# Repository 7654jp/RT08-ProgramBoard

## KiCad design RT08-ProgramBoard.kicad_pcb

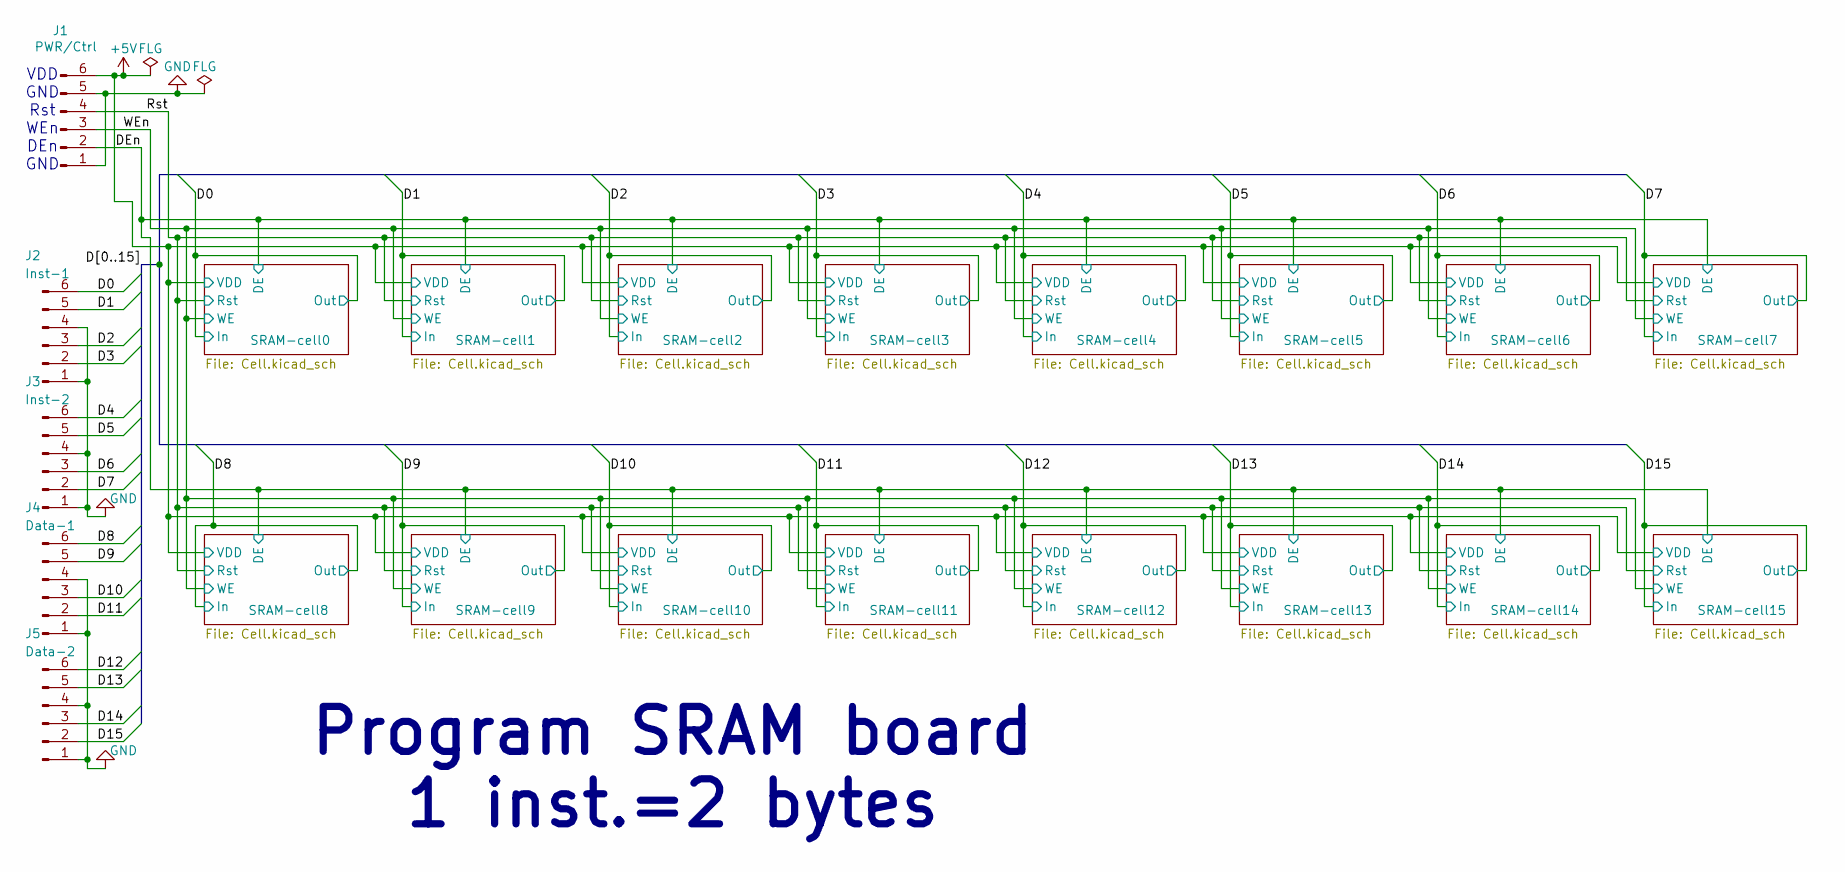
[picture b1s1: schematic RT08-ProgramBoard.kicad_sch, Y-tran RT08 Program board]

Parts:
J1: PWR/Ctrl; PinHeader_1x06_P2.54mm_Vertical
J2: Inst-1; PinHeader_1x06_P2.54mm_Vertical
J3: Inst-2; PinHeader_1x06_P2.54mm_Vertical
J4: Data-1; PinHeader_1x06_P2.54mm_Vertical
J5: Data-2; PinHeader_1x06_P2.54mm_Vertical

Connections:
+5V: J1.6; also elsewhere on the board
/D0: J2.6; also elsewhere on the board
/D1: J2.5; also elsewhere on the board
/D2: J2.3; also elsewhere on the board
/D3: J2.2; also elsewhere on the board
/D4: J3.6; also elsewhere on the board
/D5: J3.5; also elsewhere on the board
/D6: J3.3; also elsewhere on the board
/D7: J3.2; also elsewhere on the board
/D8: J4.6; also elsewhere on the board
/D9: J4.5; also elsewhere on the board
/D10: J4.3; also elsewhere on the board
/D11: J4.2; also elsewhere on the board
/D12: J5.6; also elsewhere on the board
/D13: J5.5; also elsewhere on the board
/D14: J5.3; also elsewhere on the board
/D15: J5.2; also elsewhere on the board
/DEn: J1.2; also elsewhere on the board
/Rst: J1.4; also elsewhere on the board
/WEn: J1.3; also elsewhere on the board
GND: J1.1, J1.5, J2.1, J2.4, J3.1, J3.4, J4.1, J4.4, J5.1, J5.4; also elsewhere on the board

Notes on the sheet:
VDD GND Rst WEn DEn GND
Program SRAM board 1 inst.=2 bytes

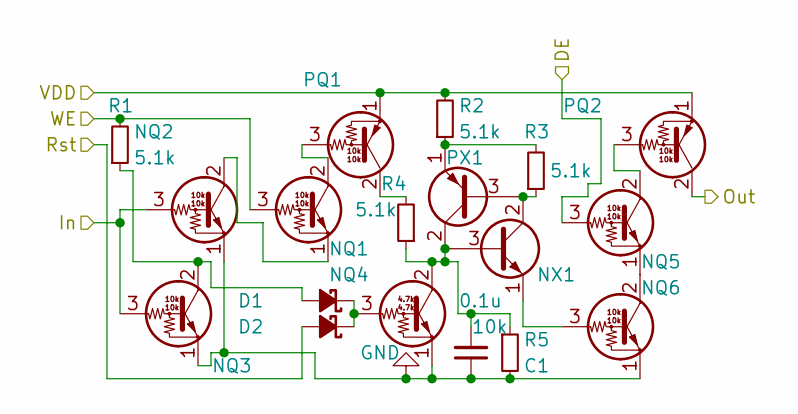
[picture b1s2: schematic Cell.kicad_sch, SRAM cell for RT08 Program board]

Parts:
C1: 0.1u; C_Disc_D3.0mm_W2.0mm_P2.50mm
D1, D2: 30V0.2A; D_DO-35_SOD27_P7.62mm_Horizontal
NQ1, NQ2, NQ3, NQ5, NQ6: DTC114E-THT; TO-92_Inline_Wide
NQ4: DTC143E-THT; TO-92_Inline_Wide
NX1: 2SC1815; TO-92_Inline_Wide
PQ1, PQ2: DTA114E-THT; TO-92_Inline_Wide
PX1: 2SA1015; TO-92_Inline_Wide
R1, R2, R3, R4: 5.1k; R_Axial_DIN0207_L6.3mm_D2.5mm_P7.62mm_Horizontal
R5: 10k; R_Axial_DIN0207_L6.3mm_D2.5mm_P7.62mm_Horizontal

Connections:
+5V: PQ1.1 (E), PQ2.1 (E), R2.2; also elsewhere on the board
/D0: NQ2.3 (B), NQ3.3 (B), PQ2.2 (C); also elsewhere on the board
/DEn: NQ5.3 (B); also elsewhere on the board
/Rst: D2.2 (A); also elsewhere on the board
/WEn: NQ1.3 (B), R1.2; also elsewhere on the board
GND: C1.1, NQ2.1 (E), NQ3.1 (E), NQ4.1 (E), NQ6.1 (E), R5.2; also elsewhere on the board
unnamed: D1.2 (A), NQ3.2 (C), R1.1
unnamed: D1.1 (K), D2.1 (K), NQ4.3 (B)
unnamed: NQ1.2 (C), PQ1.3 (B)
unnamed: NQ1.1 (E), NQ2.2 (C)
unnamed: C1.2, NQ4.2 (C), NX1.3 (B), PX1.2 (C), R4.1, R5.1
unnamed: NQ5.2 (C), PQ2.3 (B)
unnamed: NQ5.1 (E), NQ6.2 (C)
unnamed: NQ6.3 (B), NX1.1 (E)
unnamed: NX1.2 (C), PX1.3 (B), R3.1
unnamed: PQ1.2 (C), R4.2
unnamed: PX1.1 (E), R2.1, R3.2

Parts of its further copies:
C2, C3, C4, C5, C6, C7, C8, C9, C10, C11, C12, C13, C14, C15, C16: 0.1u; C_Disc_D3.0mm_W2.0mm_P2.50mm
D3, D4, D5, D6, D7, D8, D9, D10, D11, D12, D13, D14, D15, D16, D17, D18, D19, D20, D21, D22, D23, D24, D25, D26, D27, D28, D29, D30, D31, D32: 30V0.2A; D_DO-35_SOD27_P7.62mm_Horizontal
NQ7, NQ8, NQ9, NQ11, NQ12, NQ13, NQ14, NQ15, NQ17, NQ18, NQ19, NQ20, NQ21, NQ23, NQ24, NQ25, NQ26, NQ27, NQ29, NQ30, NQ31, NQ32, NQ33, NQ35, NQ36, NQ37, NQ38, NQ39, NQ41, NQ42, NQ43, NQ44, NQ45, NQ47, NQ48, NQ49, NQ50, NQ51, NQ53, NQ54, NQ55, NQ56, NQ57, NQ59, NQ60, NQ61, NQ62, NQ63, NQ65, NQ66, NQ67, NQ68, NQ69, NQ71, NQ72, NQ73, NQ74, NQ75, NQ77, NQ78, NQ79, NQ80, NQ81, NQ83, NQ84, NQ85, NQ86, NQ87, NQ89, NQ90, NQ91, NQ92, NQ93, NQ95, NQ96: DTC114E-THT; TO-92_Inline_Wide
NQ10, NQ16, NQ22, NQ28, NQ34, NQ40, NQ46, NQ52, NQ58, NQ64, NQ70, NQ76, NQ82, NQ88, NQ94: DTC143E-THT; TO-92_Inline_Wide
NX2, NX3, NX4, NX5, NX6, NX7, NX8, NX9, NX10, NX11, NX12, NX13, NX14, NX15, NX16: 2SC1815; TO-92_Inline_Wide
PQ3, PQ4, PQ5, PQ6, PQ7, PQ8, PQ9, PQ10, PQ11, PQ12, PQ13, PQ14, PQ15, PQ16, PQ17, PQ18, PQ19, PQ20, PQ21, PQ22, PQ23, PQ24, PQ25, PQ26, PQ27, PQ28, PQ29, PQ30, PQ31, PQ32: DTA114E-THT; TO-92_Inline_Wide
PX2, PX3, PX4, PX5, PX6, PX7, PX8, PX9, PX10, PX11, PX12, PX13, PX14, PX15, PX16: 2SA1015; TO-92_Inline_Wide
R6, R7, R8, R9, R11, R12, R13, R14, R16, R17, R18, R19, R21, R22, R23, R24, R26, R27, R28, R29, R31, R32, R33, R34, R36, R37, R38, R39, R41, R42, R43, R44, R46, R47, R48, R49, R51, R52, R53, R54, R56, R57, R58, R59, R61, R62, R63, R64, R66, R67, R68, R69, R71, R72, R73, R74, R76, R77, R78, R79: 5.1k; R_Axial_DIN0207_L6.3mm_D2.5mm_P7.62mm_Horizontal
R10, R15, R20, R25, R30, R35, R40, R45, R50, R55, R60, R65, R70, R75, R80: 10k; R_Axial_DIN0207_L6.3mm_D2.5mm_P7.62mm_Horizontal

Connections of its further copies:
+5V: PQ3.1 (E), PQ4.1 (E), PQ5.1 (E), PQ6.1 (E), PQ7.1 (E), PQ8.1 (E), PQ9.1 (E), PQ10.1 (E), PQ11.1 (E), PQ12.1 (E), PQ13.1 (E), PQ14.1 (E), PQ15.1 (E), PQ16.1 (E), PQ17.1 (E), PQ18.1 (E), PQ19.1 (E), PQ20.1 (E), PQ21.1 (E), PQ22.1 (E), PQ23.1 (E), PQ24.1 (E), PQ25.1 (E), PQ26.1 (E), PQ27.1 (E), PQ28.1 (E), PQ29.1 (E), PQ30.1 (E), PQ31.1 (E), PQ32.1 (E), R7.2, R12.2, R17.2, R22.2, R27.2, R32.2, R37.2, R42.2, R47.2, R52.2, R57.2, R62.2, R67.2, R72.2, R77.2; also elsewhere on the board
/D1: NQ8.3 (B), NQ9.3 (B), PQ4.2 (C); also elsewhere on the board
/D2: NQ14.3 (B), NQ15.3 (B), PQ6.2 (C); also elsewhere on the board
/D3: NQ20.3 (B), NQ21.3 (B), PQ8.2 (C); also elsewhere on the board
/D4: NQ26.3 (B), NQ27.3 (B), PQ10.2 (C); also elsewhere on the board
/D5: NQ32.3 (B), NQ33.3 (B), PQ12.2 (C); also elsewhere on the board
/D6: NQ38.3 (B), NQ39.3 (B), PQ14.2 (C); also elsewhere on the board
/D7: NQ44.3 (B), NQ45.3 (B), PQ16.2 (C); also elsewhere on the board
/D8: NQ50.3 (B), NQ51.3 (B), PQ18.2 (C); also elsewhere on the board
/D9: NQ56.3 (B), NQ57.3 (B), PQ20.2 (C); also elsewhere on the board
/D10: NQ62.3 (B), NQ63.3 (B), PQ22.2 (C); also elsewhere on the board
/D11: NQ68.3 (B), NQ69.3 (B), PQ24.2 (C); also elsewhere on the board
/D12: NQ74.3 (B), NQ75.3 (B), PQ26.2 (C); also elsewhere on the board
/D13: NQ80.3 (B), NQ81.3 (B), PQ28.2 (C); also elsewhere on the board
/D14: NQ86.3 (B), NQ87.3 (B), PQ30.2 (C); also elsewhere on the board
/D15: NQ92.3 (B), NQ93.3 (B), PQ32.2 (C); also elsewhere on the board
/DEn: NQ11.3 (B), NQ17.3 (B), NQ23.3 (B), NQ29.3 (B), NQ35.3 (B), NQ41.3 (B), NQ47.3 (B), NQ53.3 (B), NQ59.3 (B), NQ65.3 (B), NQ71.3 (B), NQ77.3 (B), NQ83.3 (B), NQ89.3 (B), NQ95.3 (B); also elsewhere on the board
/Rst: D4.2 (A), D6.2 (A), D8.2 (A), D10.2 (A), D12.2 (A), D14.2 (A), D16.2 (A), D18.2 (A), D20.2 (A), D22.2 (A), D24.2 (A), D26.2 (A), D28.2 (A), D30.2 (A), D32.2 (A); also elsewhere on the board
/WEn: NQ7.3 (B), NQ13.3 (B), NQ19.3 (B), NQ25.3 (B), NQ31.3 (B), NQ37.3 (B), NQ43.3 (B), NQ49.3 (B), NQ55.3 (B), NQ61.3 (B), NQ67.3 (B), NQ73.3 (B), NQ79.3 (B), NQ85.3 (B), NQ91.3 (B), R6.2, R11.2, R16.2, R21.2, R26.2, R31.2, R36.2, R41.2, R46.2, R51.2, R56.2, R61.2, R66.2, R71.2, R76.2; also elsewhere on the board
GND: C2.1, C3.1, C4.1, C5.1, C6.1, C7.1, C8.1, C9.1, C10.1, C11.1, C12.1, C13.1, C14.1, C15.1, C16.1, NQ8.1 (E), NQ9.1 (E), NQ10.1 (E), NQ12.1 (E), NQ14.1 (E), NQ15.1 (E), NQ16.1 (E), NQ18.1 (E), NQ20.1 (E), NQ21.1 (E), NQ22.1 (E), NQ24.1 (E), NQ26.1 (E), NQ27.1 (E), NQ28.1 (E), NQ30.1 (E), NQ32.1 (E), NQ33.1 (E), NQ34.1 (E), NQ36.1 (E), NQ38.1 (E), NQ39.1 (E), NQ40.1 (E), NQ42.1 (E), NQ44.1 (E), NQ45.1 (E), NQ46.1 (E), NQ48.1 (E), NQ50.1 (E), NQ51.1 (E), NQ52.1 (E), NQ54.1 (E), NQ56.1 (E), NQ57.1 (E), NQ58.1 (E), NQ60.1 (E), NQ62.1 (E), NQ63.1 (E), NQ64.1 (E), NQ66.1 (E), NQ68.1 (E), NQ69.1 (E), NQ70.1 (E), NQ72.1 (E), NQ74.1 (E), NQ75.1 (E), NQ76.1 (E), NQ78.1 (E), NQ80.1 (E), NQ81.1 (E), NQ82.1 (E), NQ84.1 (E), NQ86.1 (E), NQ87.1 (E), NQ88.1 (E), NQ90.1 (E), NQ92.1 (E), NQ93.1 (E), NQ94.1 (E), NQ96.1 (E), R10.2, R15.2, R20.2, R25.2, R30.2, R35.2, R40.2, R45.2, R50.2, R55.2, R60.2, R65.2, R70.2, R75.2, R80.2; also elsewhere on the board
unnamed: D3.2 (A), NQ9.2 (C), R6.1
unnamed: D3.1 (K), D4.1 (K), NQ10.3 (B)
unnamed: D5.2 (A), NQ15.2 (C), R11.1
unnamed: D5.1 (K), D6.1 (K), NQ16.3 (B)
unnamed: D7.2 (A), NQ21.2 (C), R16.1
unnamed: D7.1 (K), D8.1 (K), NQ22.3 (B)
unnamed: D9.2 (A), NQ27.2 (C), R21.1
unnamed: D9.1 (K), D10.1 (K), NQ28.3 (B)
unnamed: D11.2 (A), NQ33.2 (C), R26.1
unnamed: D11.1 (K), D12.1 (K), NQ34.3 (B)
unnamed: D13.2 (A), NQ39.2 (C), R31.1
unnamed: D13.1 (K), D14.1 (K), NQ40.3 (B)
unnamed: D15.2 (A), NQ45.2 (C), R36.1
unnamed: D15.1 (K), D16.1 (K), NQ46.3 (B)
unnamed: D17.2 (A), NQ51.2 (C), R41.1
unnamed: D17.1 (K), D18.1 (K), NQ52.3 (B)
unnamed: D19.2 (A), NQ57.2 (C), R46.1
unnamed: D19.1 (K), D20.1 (K), NQ58.3 (B)
unnamed: D21.2 (A), NQ63.2 (C), R51.1
unnamed: D21.1 (K), D22.1 (K), NQ64.3 (B)
unnamed: D23.2 (A), NQ69.2 (C), R56.1
unnamed: D23.1 (K), D24.1 (K), NQ70.3 (B)
unnamed: D25.2 (A), NQ75.2 (C), R61.1
unnamed: D25.1 (K), D26.1 (K), NQ76.3 (B)
unnamed: D27.2 (A), NQ81.2 (C), R66.1
unnamed: D27.1 (K), D28.1 (K), NQ82.3 (B)
unnamed: D29.2 (A), NQ87.2 (C), R71.1
unnamed: D29.1 (K), D30.1 (K), NQ88.3 (B)
unnamed: D31.2 (A), NQ93.2 (C), R76.1
unnamed: D31.1 (K), D32.1 (K), NQ94.3 (B)
unnamed: NQ7.2 (C), PQ3.3 (B)
unnamed: NQ7.1 (E), NQ8.2 (C)
unnamed: C2.2, NQ10.2 (C), NX2.3 (B), PX2.2 (C), R9.1, R10.1
unnamed: NQ11.2 (C), PQ4.3 (B)
unnamed: NQ11.1 (E), NQ12.2 (C)
unnamed: NQ12.3 (B), NX2.1 (E)
unnamed: NQ13.2 (C), PQ5.3 (B)
unnamed: NQ13.1 (E), NQ14.2 (C)
unnamed: C3.2, NQ16.2 (C), NX3.3 (B), PX3.2 (C), R14.1, R15.1
unnamed: NQ17.2 (C), PQ6.3 (B)
unnamed: NQ17.1 (E), NQ18.2 (C)
unnamed: NQ18.3 (B), NX3.1 (E)
unnamed: NQ19.2 (C), PQ7.3 (B)
unnamed: NQ19.1 (E), NQ20.2 (C)
unnamed: C4.2, NQ22.2 (C), NX4.3 (B), PX4.2 (C), R19.1, R20.1
unnamed: NQ23.2 (C), PQ8.3 (B)
unnamed: NQ23.1 (E), NQ24.2 (C)
unnamed: NQ24.3 (B), NX4.1 (E)
unnamed: NQ25.2 (C), PQ9.3 (B)
unnamed: NQ25.1 (E), NQ26.2 (C)
unnamed: C5.2, NQ28.2 (C), NX5.3 (B), PX5.2 (C), R24.1, R25.1
unnamed: NQ29.2 (C), PQ10.3 (B)
unnamed: NQ29.1 (E), NQ30.2 (C)
unnamed: NQ30.3 (B), NX5.1 (E)
unnamed: NQ31.2 (C), PQ11.3 (B)
unnamed: NQ31.1 (E), NQ32.2 (C)
unnamed: C6.2, NQ34.2 (C), NX6.3 (B), PX6.2 (C), R29.1, R30.1
unnamed: NQ35.2 (C), PQ12.3 (B)
unnamed: NQ35.1 (E), NQ36.2 (C)
unnamed: NQ36.3 (B), NX6.1 (E)
unnamed: NQ37.2 (C), PQ13.3 (B)
unnamed: NQ37.1 (E), NQ38.2 (C)
unnamed: C7.2, NQ40.2 (C), NX7.3 (B), PX7.2 (C), R34.1, R35.1
unnamed: NQ41.2 (C), PQ14.3 (B)
unnamed: NQ41.1 (E), NQ42.2 (C)
unnamed: NQ42.3 (B), NX7.1 (E)
unnamed: NQ43.2 (C), PQ15.3 (B)
unnamed: NQ43.1 (E), NQ44.2 (C)
unnamed: C8.2, NQ46.2 (C), NX8.3 (B), PX8.2 (C), R39.1, R40.1
unnamed: NQ47.2 (C), PQ16.3 (B)
unnamed: NQ47.1 (E), NQ48.2 (C)
unnamed: NQ48.3 (B), NX8.1 (E)
unnamed: NQ49.2 (C), PQ17.3 (B)
unnamed: NQ49.1 (E), NQ50.2 (C)
unnamed: C9.2, NQ52.2 (C), NX9.3 (B), PX9.2 (C), R44.1, R45.1
unnamed: NQ53.2 (C), PQ18.3 (B)
unnamed: NQ53.1 (E), NQ54.2 (C)
unnamed: NQ54.3 (B), NX9.1 (E)
unnamed: NQ55.2 (C), PQ19.3 (B)
unnamed: NQ55.1 (E), NQ56.2 (C)
unnamed: C10.2, NQ58.2 (C), NX10.3 (B), PX10.2 (C), R49.1, R50.1
unnamed: NQ59.2 (C), PQ20.3 (B)
unnamed: NQ59.1 (E), NQ60.2 (C)
unnamed: NQ60.3 (B), NX10.1 (E)
unnamed: NQ61.2 (C), PQ21.3 (B)
unnamed: NQ61.1 (E), NQ62.2 (C)
unnamed: C11.2, NQ64.2 (C), NX11.3 (B), PX11.2 (C), R54.1, R55.1
unnamed: NQ65.2 (C), PQ22.3 (B)
unnamed: NQ65.1 (E), NQ66.2 (C)
unnamed: NQ66.3 (B), NX11.1 (E)
unnamed: NQ67.2 (C), PQ23.3 (B)
unnamed: NQ67.1 (E), NQ68.2 (C)
unnamed: C12.2, NQ70.2 (C), NX12.3 (B), PX12.2 (C), R59.1, R60.1
unnamed: NQ71.2 (C), PQ24.3 (B)
unnamed: NQ71.1 (E), NQ72.2 (C)
unnamed: NQ72.3 (B), NX12.1 (E)
unnamed: NQ73.2 (C), PQ25.3 (B)
unnamed: NQ73.1 (E), NQ74.2 (C)
unnamed: C13.2, NQ76.2 (C), NX13.3 (B), PX13.2 (C), R64.1, R65.1
unnamed: NQ77.2 (C), PQ26.3 (B)
unnamed: NQ77.1 (E), NQ78.2 (C)
unnamed: NQ78.3 (B), NX13.1 (E)
unnamed: NQ79.2 (C), PQ27.3 (B)
unnamed: NQ79.1 (E), NQ80.2 (C)
unnamed: C14.2, NQ82.2 (C), NX14.3 (B), PX14.2 (C), R69.1, R70.1
unnamed: NQ83.2 (C), PQ28.3 (B)
unnamed: NQ83.1 (E), NQ84.2 (C)
unnamed: NQ84.3 (B), NX14.1 (E)
unnamed: NQ85.2 (C), PQ29.3 (B)
unnamed: NQ85.1 (E), NQ86.2 (C)
unnamed: C15.2, NQ88.2 (C), NX15.3 (B), PX15.2 (C), R74.1, R75.1
unnamed: NQ89.2 (C), PQ30.3 (B)
unnamed: NQ89.1 (E), NQ90.2 (C)
unnamed: NQ90.3 (B), NX15.1 (E)
unnamed: NQ91.2 (C), PQ31.3 (B)
unnamed: NQ91.1 (E), NQ92.2 (C)
unnamed: C16.2, NQ94.2 (C), NX16.3 (B), PX16.2 (C), R79.1, R80.1
unnamed: NQ95.2 (C), PQ32.3 (B)
unnamed: NQ95.1 (E), NQ96.2 (C)
unnamed: NQ96.3 (B), NX16.1 (E)
unnamed: NX2.2 (C), PX2.3 (B), R8.1
unnamed: NX3.2 (C), PX3.3 (B), R13.1
unnamed: NX4.2 (C), PX4.3 (B), R18.1
unnamed: NX5.2 (C), PX5.3 (B), R23.1
unnamed: NX6.2 (C), PX6.3 (B), R28.1
unnamed: NX7.2 (C), PX7.3 (B), R33.1
unnamed: NX8.2 (C), PX8.3 (B), R38.1
unnamed: NX9.2 (C), PX9.3 (B), R43.1
unnamed: NX10.2 (C), PX10.3 (B), R48.1
unnamed: NX11.2 (C), PX11.3 (B), R53.1
unnamed: NX12.2 (C), PX12.3 (B), R58.1
unnamed: NX13.2 (C), PX13.3 (B), R63.1
unnamed: NX14.2 (C), PX14.3 (B), R68.1
unnamed: NX15.2 (C), PX15.3 (B), R73.1
unnamed: NX16.2 (C), PX16.3 (B), R78.1
unnamed: PQ3.2 (C), R9.2
unnamed: PQ5.2 (C), R14.2
unnamed: PQ7.2 (C), R19.2
unnamed: PQ9.2 (C), R24.2
unnamed: PQ11.2 (C), R29.2
unnamed: PQ13.2 (C), R34.2
unnamed: PQ15.2 (C), R39.2
unnamed: PQ17.2 (C), R44.2
unnamed: PQ19.2 (C), R49.2
unnamed: PQ21.2 (C), R54.2
unnamed: PQ23.2 (C), R59.2
unnamed: PQ25.2 (C), R64.2
unnamed: PQ27.2 (C), R69.2
unnamed: PQ29.2 (C), R74.2
unnamed: PQ31.2 (C), R79.2
unnamed: PX2.1 (E), R7.1, R8.2
unnamed: PX3.1 (E), R12.1, R13.2
unnamed: PX4.1 (E), R17.1, R18.2
unnamed: PX5.1 (E), R22.1, R23.2
unnamed: PX6.1 (E), R27.1, R28.2
unnamed: PX7.1 (E), R32.1, R33.2
unnamed: PX8.1 (E), R37.1, R38.2
unnamed: PX9.1 (E), R42.1, R43.2
unnamed: PX10.1 (E), R47.1, R48.2
unnamed: PX11.1 (E), R52.1, R53.2
unnamed: PX12.1 (E), R57.1, R58.2
unnamed: PX13.1 (E), R62.1, R63.2
unnamed: PX14.1 (E), R67.1, R68.2
unnamed: PX15.1 (E), R72.1, R73.2
unnamed: PX16.1 (E), R77.1, R78.2

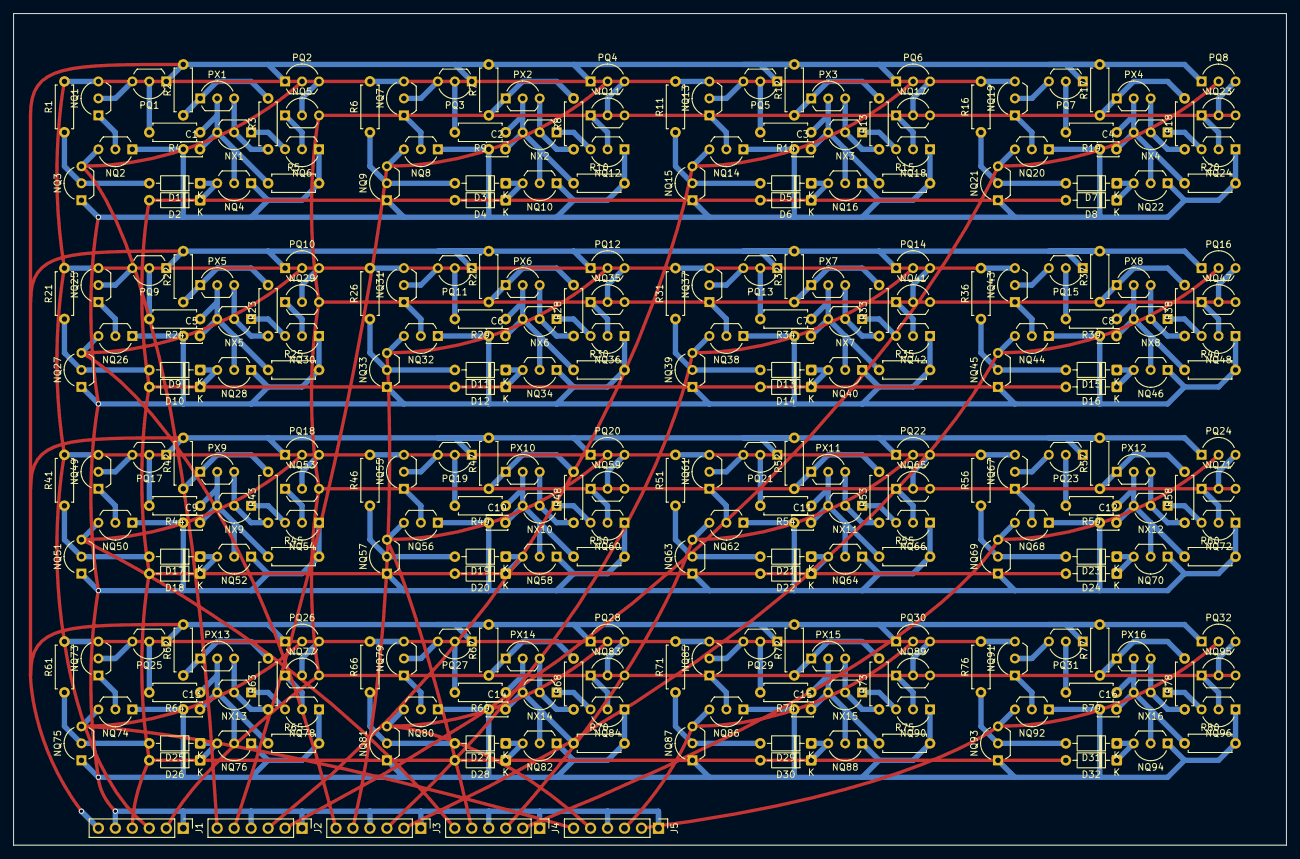
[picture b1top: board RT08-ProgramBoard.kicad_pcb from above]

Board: 2 copper layers, 190.5 x 124.5 mm, 293 parts (0 on the bottom side), 197 nets.

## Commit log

2025-04-28 Added 1 inst.:2 bytes SRAM
2025-04-30 Re-edit the cell, change to matrix
2025-05-02 Re-re-edit the cell, optimize complete
2025-05-02 16x16 matrix done, next: IO/Controller
2025-05-05 Mid-editing IO/Ctrl, for share
2025-05-06 Schematics complete, I think.
2025-05-06 Edit the cell more, apply data 0
2025-05-07 Cell edit complete, re-building matrix
2025-05-08 Rebuilding matrix 1 col done
2025-05-10 Schematics re-completed, annotation done
2025-05-11 Added parts to pcb file, and some stuff
2025-05-12 Changed 16x16 to 8x16, re-added parts
2025-05-13 Started editing PCB
2025-05-14 Edited PCB a bit
2025-05-15 A little edit
2025-05-16 Deleted one of two IO pull-down
2025-05-24 Started applying 'sub-schematics' to main schematic file
2025-05-25 Schematics editing
2025-05-27 Schematics with 'sub-schematics' almost done
2025-05-28 Finished editing .sch
2025-05-29 Editing PCB, 1 cell temp-done
2025-05-30 Editing PCB, duplicating
2025-05-30 Edited title n' stuff
2025-05-31 Editing PCB, stuck with duplicating stuff
2025-06-01 Editing PCB, duplicating stuff solved, 1 cell almost-done
2025-06-03 Adding buffer to Rst signal
2025-06-05 Edited Sch, changed buffer from daisy chain to get from root
2025-06-09 Editing PCB, one line almost-done?
2025-06-10 Editing pcb, changed 1 SRAM-line per inst. to 2 line per inst. too wide lol
2025-06-12 Editing PCB, second line
2025-06-12 True second line
2025-06-13 Editing PCB, third inst. maybe 8->4 inst. per board
2025-06-13 Third inst. starting
2025-06-13 Editing PCB, fourth line done, thinking of 4 inst. per board
2025-06-14 Editing PCB, RST signal multiplier added to 4 lines
2025-06-15 Changing from 8x16 to 4x16, size issue
2025-06-16 Updated sch, re-create pcb next
2025-06-17 Editing PCB, 2to4 encoder temp-done
2025-06-18 PCB no longer will be used, I'm building it with universal one instead
2025-06-19 Changed size, 1 inst per board. Updating everything
2025-06-20 Deleted one group, ready to re-builded
2025-06-22 Optimized for univ. board
2025-06-26 Share footprint folder
2025-06-28 Assembled 4 cells, fp copied
2025-06-30 Did some stuff, started wiring
2025-07-02 Editing Board, VDD and VCC wiring done
2025-07-04 Editing board, size-optimizing
2025-07-06 Seems done!
2025-07-11 Moved a bit, updated things.csv
2025-07-28 Edited pinouts so it can be connected.
2025-08-05 Deleted '-' from its name, officially
2025-08-11 Updated pinouts n' something
2025-08-12 Changed pinheaders
2025-08-19 Adding one more parts per bit, editing PCB
2025-08-20 Finished editing PCB
2025-08-20 Merged In/Out pins to one pin groups!
2025-08-20 Chaned sch size
2026-01-03 Added License
    Added CERN Open Hardware Licence Version 2 - Permissive to the project.
2026-06-20 Remaking due to design change, wip1
2026-06-22 Designing new register circuit
2026-06-30 New design completed
